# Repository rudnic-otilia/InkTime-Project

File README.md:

# InkTime

Smartwatch open-source bazat pe nRF52840, cu display e-paper.

## Diagramă Bloc

## BOM (Bill of Materials)

## Componente principale

| Referinta | Componenta | Descriere | Package | Cantitate | JLCPCB / LCSC | Datasheet |
|-----------|-----------|-----------|---------|-----------|---------------|-----------|
| U1 | NRF52840-QIAA-R | MCU principal + BLE 5.0 + USB nativ | aQFN-73 (7×7mm) | 1 | [C190794](https://jlcpcb.com/partdetail/NordicSemicon-NRF52840_QIAAR/C190794) | [Datasheet](https://infocenter.nordicsemi.com/pdf/nRF52840_PS_v1.7.pdf) |
| IC1 | BQ25180YBGR | Charger LiPo cu power-path, I2C | DSBGA-8 (1.6×1.1mm) | 1 | [C3682423](https://jlcpcb.com/partdetail/TexasInstruments-BQ25180YBGR/C3682423) | [Datasheet](https://www.ti.com/lit/ds/symlink/bq25180.pdf) |
| IC9 | RT6160AWSC | Buck-boost regulator 3.3V, I2C | WLCSP-15 (1.4×2.3mm) | 1 | [C7065276](https://jlcpcb.com/partdetail/RichTek-RT6160AWSC/C7065276) | [Datasheet](https://www.richtek.com/assets/product_file/RT6160A/DS6160A-00.pdf) |
| U3 | MAX17048G+T10 | Fuel gauge baterie LiPo, I2C | DFN-8 (2×2mm) | 1 | [C2682616](https://jlcpcb.com/partdetail/MaximIntegrated-MAX17048GT10/C2682616) | [Datasheet](https://www.analog.com/media/en/technical-documentation/data-sheets/MAX17048-MAX17049.pdf) |
| IC3 | BMA423 | Accelerometru 3-axe + pedometru, I2C | LGA-12 (2×2mm) | 1 | [C189517](https://jlcpcb.com/partdetail/BoschSensortec-BMA423/C189517) | [Datasheet](https://www.lcsc.com/datasheet/C189517.pdf) |
| IC2 | DRV2605YZFR | Haptic driver pentru motor ERM, I2C | DSBGA-9 (1.44×1.44mm) | 1 | [C81079](https://jlcpcb.com/partdetail/TexasInstruments-DRV2605YZFR/C81079) | [Datasheet](https://www.ti.com/lit/ds/symlink/drv2605.pdf) |
| D3 | USBLC6-2SC6Y | Protecție ESD linii USB D+/D- | SOT-23-6 | 1 | [C5310974](https://jlcpcb.com/partdetail/TECHPUBLIC-USBLC62SC6Y/C5310974) | [Datasheet](https://www.st.com/resource/en/datasheet/usblc6-2.pdf) |
| Q3 | SI1308EDL-T1-GE3 | N-channel MOSFET, power gate e-paper | SC-70-3 | 1 | [C10487](https://jlcpcb.com/partdetail/VishayIntertech-SI1308EDLT1GE3/C10487) | [Datasheet](https://www.vishay.com/docs/63587/si1308edl.pdf) |
| Q1 | DMG2305UX-7 | P-channel MOSFET, power switch | SOT-23-3 | 1 | [C252544](https://jlcpcb.com/partdetail/Diodes-DMG2305UXT116/C252544) | [Datasheet](https://www.diodes.com/assets/Datasheets/DMG2305UX.pdf) |
| J4 | KH-TYPE-C-16P | Conector USB-C 16 pini | SMD | 1 | [C2765186](https://jlcpcb.com/partdetail/Kinghelm-KH_TYPEC_16P/C2765186) | [Datasheet](https://www.kinghelm.net/usb-connectors/kh-type-c-16p.html) |
| J1 | 503480-2400 | Conector FPC 0.5mm 24 pini, pentru display e-paper | SMD | 1 | [C262280](https://jlcpcb.com/partdetail/Molex-5034802400/C262280) | [Datasheet](https://www.molex.com/en-us/products/part-detail/503480-2400) |
| J2 | TC2030-IDC | Conector Tag-Connect SWD debug/programare | PCB footprint | 1 | — | [Datasheet](https://www.tag-connect.com/wp-content/uploads/bsk-pdf-manager/TC2030-IDC_1.pdf) |
| ANT1 | 2450AT18B100E | Antenă chip 2.4GHz pentru BLE | SMD | 1 | [C89771](https://jlcpcb.com/partdetail/Johanson-2450AT18B100E/C89771) | [Datasheet](https://www.johansontechnology.com/datasheets/2450AT18B100E/2450AT18B100E.pdf) |
| X1 | X322516MLB4SI | Crystal HFXO 32MHz, 8pF, ±10ppm pentru nRF52840 | SMD 2016 | 1 | [C13738](https://jlcpcb.com/partdetail/YangxingTech-X322516MLB4SI/C13738) | [Datasheet](https://datasheet.lcsc.com/lcsc/2110221730_YXC-X322516MLB4SI_C13738.pdf) |
| X2 | Q13FC13500004 | Crystal LFXO 32.768kHz, 12.5pF, ±20ppm pentru RTC | SMD 3215 | 1 | [C32346](https://jlcpcb.com/partdetail/Epson-Q13FC13500004/C32346) | [Datasheet](https://www.lcsc.com/datasheet/C32346.pdf) |
| SW_UP, SW_DN, SW_ENT | EVP-AKE31A | Butoane tactile SMD | SMD | 3 | [C3669064](https://jlcpcb.com/partdetail/Panasonic-EVPAKE31A/C3669064) | [Datasheet](https://industrial.panasonic.com/cdbs/www-data/pdf/ATV0000/ATV0000CE5.pdf) |
| D2, D4, D5 | MBR0530 | Diodă Schottky 0.5A 30V, circuit drive e-paper | SOD-123 | 3 | [C424058](https://jlcpcb.com/partdetail/onsemi-MBR0530T1G/C424058) | [Datasheet](https://www.onsemi.com/pdf/datasheet/mbr0530t1-d.pdf) |
| L7 | FTC252012SR47MBCA | Inductor 0.47µH pentru DC/DC | 0402 | 1 | [C408368](https://jlcpcb.com/partdetail/C408368) | — |
| L5 | Inductor 68µH | Inductor boost pentru circuit drive e-paper | SMD | 1 | — | — |

---

## Pasive (rezistențe și condensatoare)

| Referință | Valoare | Package | Cantitate | Notă |
|-----------|---------|---------|-----------|------|
| C1, C2, C17, C18 | 12pF | 0201 / 0402 | 4 | Load caps cristale |
| C3, C4 | 1pF | 0201 | 2 | RF matching |
| C5, C7, C8, C12, C19 | 100nF | 0201 / 0402 | 5 | Decoupling MCU |
| C6, C20, C21, C14, C43 | 4.7µF | 0402 | 5 | Bulk decoupling |
| C9 | 820pF | 0201 | 1 | RF matching |
| C11 | 100pF | 0201 | 1 | Decoupling |
| C15 | 1.0µF | 0201 | 1 | Decoupling |
| C16 | 47nF | 0201 | 1 | Decoupling |
| C24, C39 | 10µF | 0402 | 2 | Bulk decoupling |
| C25, C33 | 22µF | 0402 | 2 | Output caps RT6160 |
| C23, C27, C34, C32, C37, C38 | 0.1µF / 1µF | 0201 | 6 | Decoupling PMIC |
| C29, C30, C31, C42 | 1µF / 0.1µF | 0201 | 4 | Decoupling diverși |
| C1-EP-DR | 10µF | 0402 | 1 | Circuit drive EPD |
| C2-EP-DR | 4.7µF/25V | 0402 | 1 | Circuit drive EPD |
| EPD_C1...C12 | 1µF/50V, 0.1µF/50V | 0402 | 10 | Condensatoare display |
| R17, R18 | 3K3 | 0201 | 2 | Pull-up I2C |
| R5, R7, R8, R9, R_PWR_EPD, R2_EP_DR | 10K | 0201 | 6 | Pull-up / bias |
| R1_USB, R2_USB | 5K1 | 0201 | 2 | CC pins USB-C |
| R_TYPE_SEL | 2.2Ω | 0201 | 1 | Selecție tip charger |
| R1_EP_DR | 0.47Ω | 0201 | 1 | Sense rezistor EPD |
| R2, R3, R4 | 0Ω | 0201 | 3 | Jumperi / DNP |
| L1 | 3.9nH | 0201 | 1 | RF matching |
| L2 | 10µH | 0402 | 1 | DC/DC inductor MCU |
| L3 | 15nH | 0402 | 1 | RF matching |

---

# Descriere Hardware

## MCU — nRF52840

Microcontrollerul principal este nRF52840 de la Nordic Semiconductor, un ARM Cortex-M4 la 64 MHz cu BLE 5.0 si USB nativ integrate. Are 1 MB Flash si 256 KB RAM. A fost ales pentru ca include tot ce e necesar intr-un singur chip: procesor, radio BLE si USB, ceea ce simplifica mult designul unui smartwatch.

Are doua cristale externe obligatorii: unul de 32 MHz pentru BLE si USB, si unul de 32.768 kHz pentru ceasul in timp real (RTC) care mentine ora cand dispozitivul doarme.

Consumul in deep sleep este sub 2 uA, ceea ce il face potrivit pentru un dispozitiv cu baterie mica.

---

## Magistrala I2C

Majoritatea componentelor comunica cu MCU-ul prin I2C pe pinii P0.06 (SDA) si P0.07 (SCL), cu rezistente pull-up de 3.3K. Fiecare componenta are o adresa unica:

| Componenta | Rol | Adresa |
|---|---|---|
| BQ25180 | Charger baterie | 0x6A |
| RT6160 | Regulator 3.3V | 0x75 |
| MAX17048 | Nivel baterie | 0x36 |
| BMA423 | Accelerometru | 0x18 |
| DRV2605 | Motor vibratii | 0x5A |

---

## Display E-Paper

Display-ul de 1.54" (200x200 pixeli) este conectat prin SPI (SCK pe P0.02, MOSI pe P0.03, plus pini de control CS/DC/RST/BUSY). Avantajul e-paper-ului este ca nu consuma energie cand imaginea sta pe loc — consuma doar la refresh.

Alimentarea display-ului este controlata printr-un MOSFET (P1.01) care il opreste complet intre refresh-uri. Se face un refresh partial o data pe minut pentru a actualiza ora, si un full refresh mai rar pentru a elimina ghosting-ul.

---

## Alimentare

Lantul de alimentare functioneaza asa: USB-C (5V) → BQ25180 (incarca bateria si alimenteaza sistemul) → RT6160 (converteste tensiunea bateriei la 3.3V fix) → toate componentele.

BQ25180 are un circuit de power-path, adica sistemul functioneaza si fara baterie daca e conectat la USB. MAX17048 masoara nivelul bateriei si trimite o intrerupere la MCU cand bateria e aproape descarcata.

Pe liniile USB exista o dioda ESD (USBLC6-2SC6Y) care protejeaza circuitul impotriva descarcarilor electrostatice.

---

## Senzori si periferice

**BMA423** — accelerometru cu pedometru hardware integrat. Numara pasii independent, fara sa trezeasca MCU-ul. Trezeste MCU-ul printr-o intrerupere pe P0.08 cand detecteaza miscare sau un anumit numar de pasi.

**DRV2605** — driver pentru motorul de vibratie. MCU-ul ii trimite prin I2C un ID de efect, iar DRV2605 il executa autonom din biblioteca sa de 123 de efecte stocate intern.

**Butoane** — trei butoane (Sus/Jos/Enter) conectate active-low la GND pe pinii P0.13, P0.14 si P1.00. Pot trezi MCU-ul din sleep.

---

## Consum estimat

| Stare | Curent | Timp/zi |
|---|---|---|
| Deep sleep | ~8 uA | ~24h |
| Refresh display (1x/min) | ~8 mA | ~60s total |
| Notificare (BLE + display + vibratii) | ~15 mA | ~100s total |

Total estimat: ~2 mAh/zi → pe o baterie de 250 mAh rezulta o autonomie teoretica de peste 100 de zile. In practica, cu pierderile reale, targetul este de 30 de zile conform specificatiilor proiectului.

# Pini nRF52840 folositi

## I2C — P0.06 (SDA) si P0.07 (SCL)

Acesti doi pini sunt folositi de toate componentele care comunica prin I2C: charger-ul BQ25180,
regulatorul RT6160, fuel gauge-ul MAX17048, accelerometrul BMA423 si driverul haptic DRV2605.
Sunt pini de uz general cu suport hardware I2C si sunt plasati convenabil in schema pentru
rutarea PCB-ului. Pull-up-urile de 3.3K sunt necesare pentru ca I2C are iesiri open-drain.

## SPI — P0.02 (SCK), P0.03 (MOSI), P0.05 (CS)

Folositi pentru comunicatia cu display-ul e-paper. SPI a fost ales in loc de I2C pentru display
deoarece este mult mai rapid, important la refresh-ul imaginii. CS (chip select) pe P0.05
activeaza display-ul doar cand MCU-ul vrea sa ii trimita date.

## Pini de control display — P0.15 (DC), P0.16 (RST), P0.17 (BUSY)

- **DC** (Data/Command): ii spune display-ului daca ce primeste este o comanda sau date de imagine
- **RST** (Reset): reseteaza display-ul la pornire sau dupa o eroare
- **BUSY**: display-ul tine acest pin activ cat timp proceseaza un refresh; MCU-ul asteapta sa
  se elibereze inainte sa trimita date noi

## Power gate display — P1.01

Controleaza MOSFET-ul care opreste alimentarea display-ului cand nu e folosit. Implicit OFF la
reset, activat doar in timpul unui refresh. Economiseste energie intre actualizari.

## Intreruperi

- **P0.08 — BMA423 INT1**: trezeste MCU-ul din deep sleep la detectia de miscare sau pas.
  Folosit ca sursa principala de wake-up pentru activitate fizica.
- **P1.08 — BMA423 INT2**: intrerupere secundara pentru evenimente avansate ale accelerometrului.
- **P0.10 — MAX17048 ALRT**: MCU-ul este notificat cand bateria scade sub un prag configurat,
  pentru a afisa avertismentul de baterie descarcata.
- **P0.11 — BQ25180 /INT**: notifica MCU-ul la evenimente de incarcare (USB conectat/deconectat,
  incarcare completa, eroare).

## Haptic enable — P0.12

Controleaza pinul EN al DRV2605. Cand nu e niciun eveniment haptic, acest pin e LOW si driverul
consuma sub 1 uA. MCU-ul il ridica la HIGH doar inainte sa trimita o comanda de vibratie.

## Butoane — P0.13, P0.14, P1.00

- **P0.13** — buton Sus
- **P0.14** — buton Jos
- **P1.00** — buton Enter / Esc

Toti trei sunt configurati cu pull-up intern si wake-on-low, adica o apasare de buton trezeste
MCU-ul direct din deep sleep fara consum suplimentar.

## USB — USBDP / USBDM (D+ / D-)

Pini dedicati USB ai nRF52840, rutati diferential la conectorul USB-C prin dioda ESD. Folositi
pentru programarea firmware-ului si optional pentru comunicatie cu PC-ul.

## SWD — SWDIO, SWDCLK, nRESET

Pini dedicati de debug si programare, conectati la conectorul TC2030. Folositi cu un programator
J-Link pentru a incarca firmware-ul si pentru debugging in timp real.

# Design Decisions — DRC Approved Errors

DRC-ul a returnat 0 erori si 85 aprobate. Motivele aprobarii:

- **Overlap (35) si Board Outline Clearance (40)**: provin din pozitia butoanelor, care a fost
  stabilita ca cerinta de proiect si nu poate fi modificata.

- **Copper Clearance (9)**: vias-uri care se intersecteaza

- **Copper - Restrict Clearance (1)**: zona restrictionata definita intentionat in jurul antenei
  BLE pentru izolarea ground plane-ului, conform recomandarilor Nordic Semiconductor.

Apache 2.0 — vezi [LICENSE](LICENSE)

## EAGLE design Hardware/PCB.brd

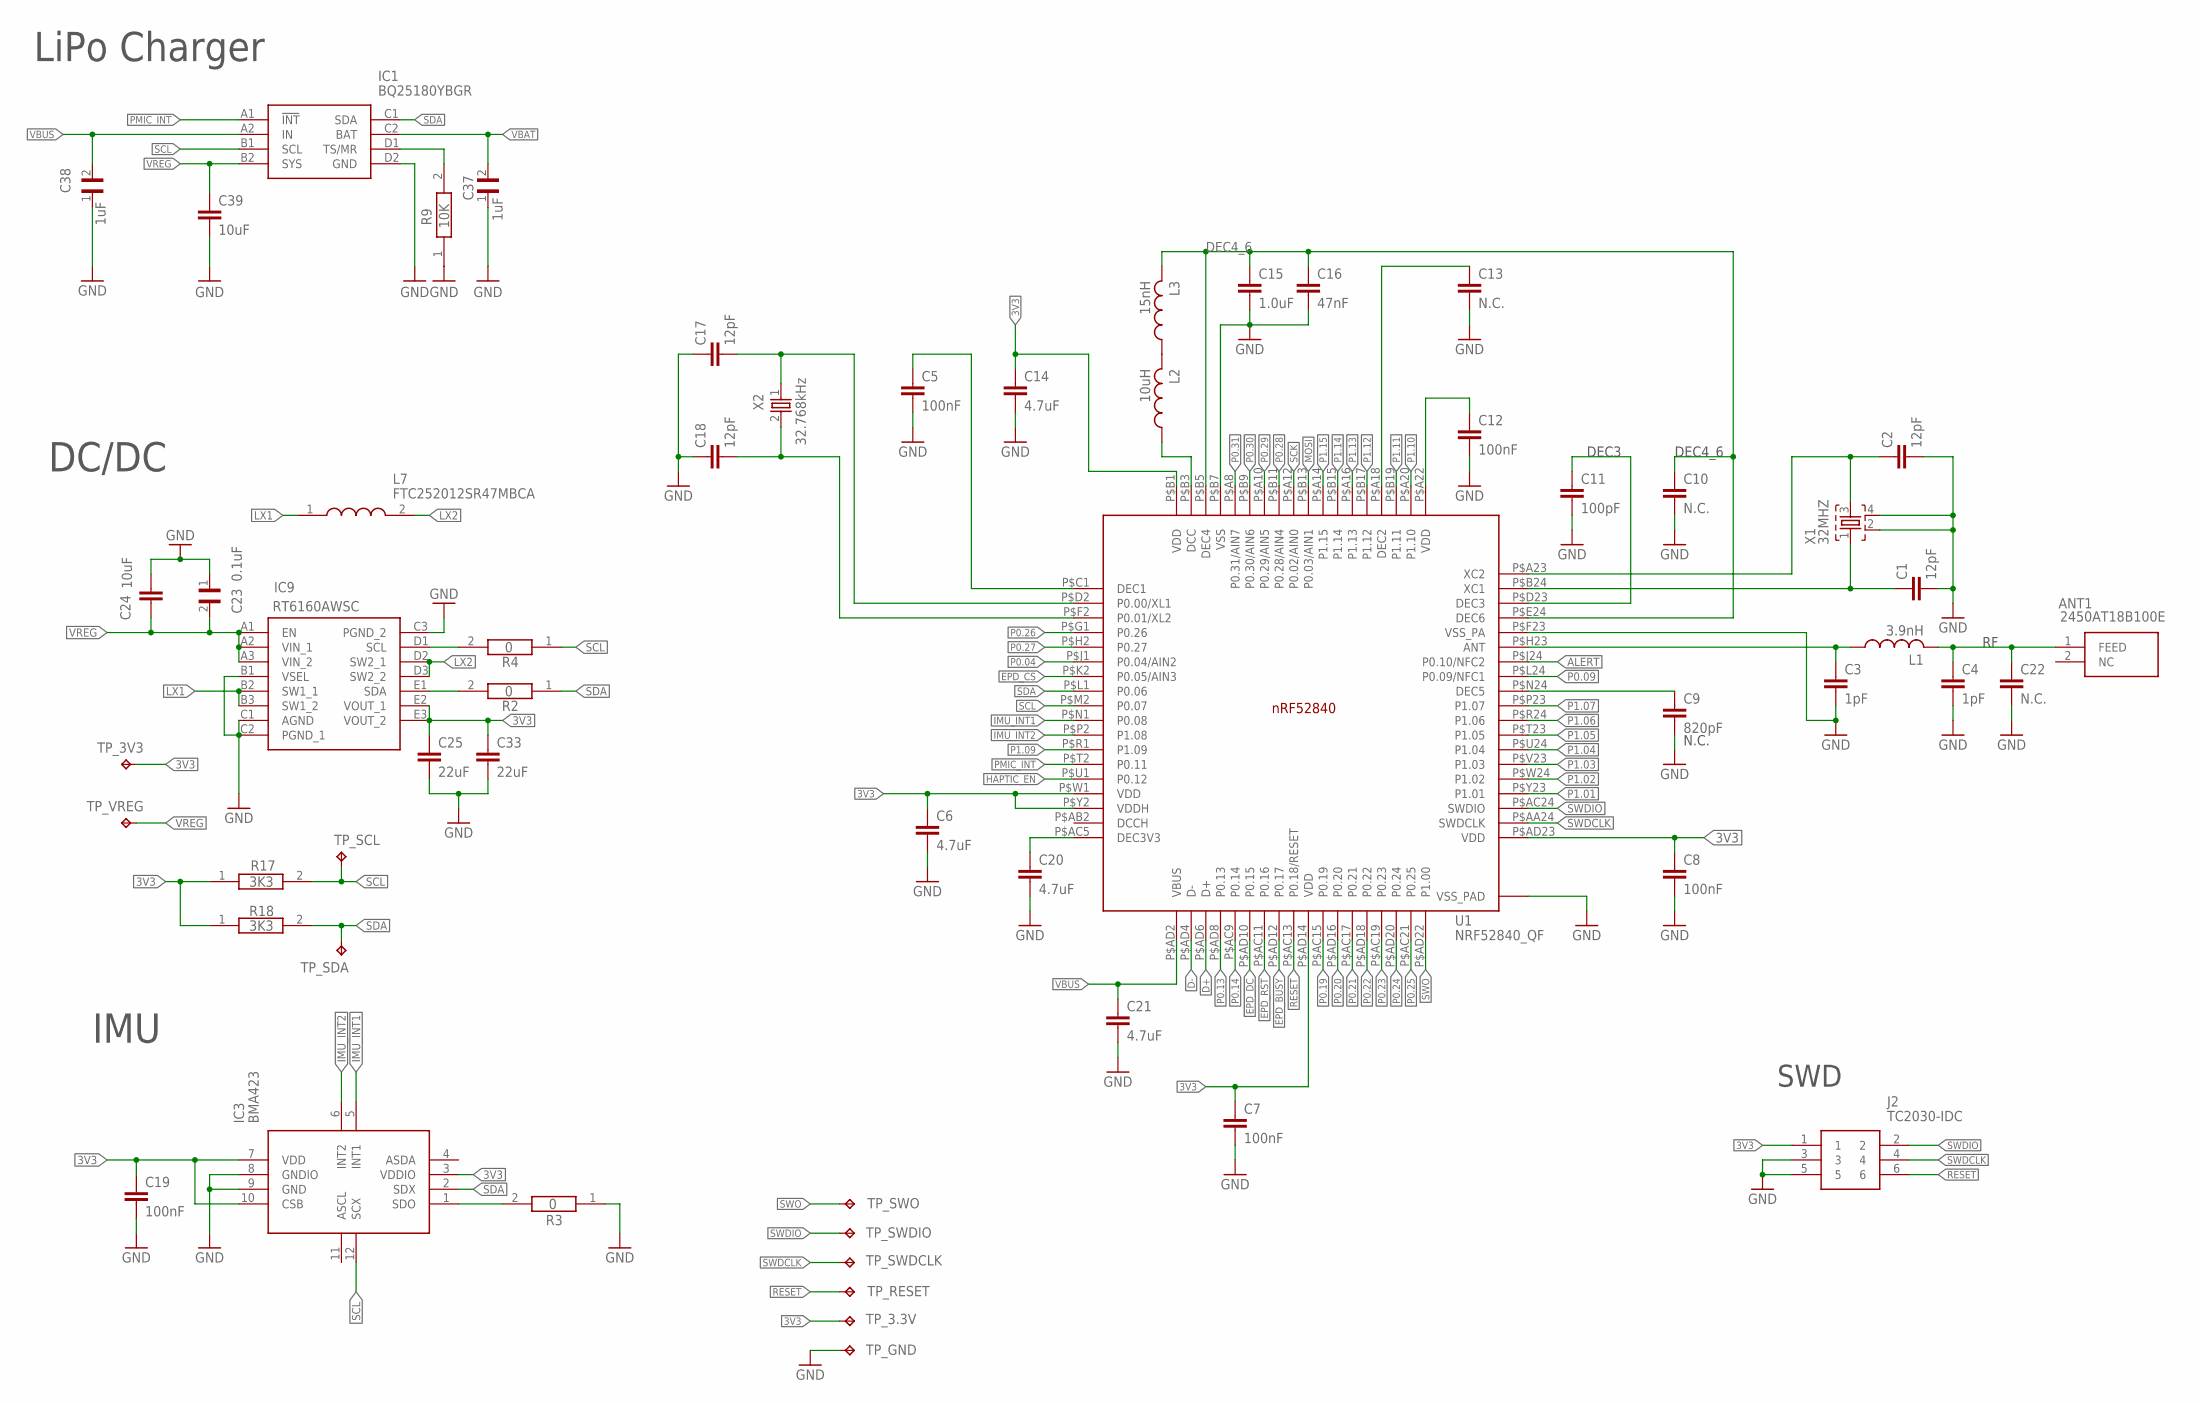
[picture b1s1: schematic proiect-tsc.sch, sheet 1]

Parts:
ANT1: 2450AT18B100E; 2450AT18B100E_ANTC3216X140N
C1, C2: 12pF; NORDIC_NRF_3_RESC0201_L
C3, C4: 1pF; NORDIC_NRF_3_RESC0201_L
C5, C7, C8, C12: 100nF; NORDIC_NRF_3_RESC0201_L
C6, C20, C21: 4.7uF; NORDIC_NRF_3_RESC0402_L
C9: 820pF; NORDIC_NRF_3_RESC0201_L
C10, C13, C22: N.C.; NORDIC_NRF_3_RESC0201_L
C11: 100pF; NORDIC_NRF_3_RESC0201_L
C14: 4.7uF; NORDIC_NRF_3_RESC0201_L
C15: 1.0uF; NORDIC_NRF_3_RESC0201_L
C16: 47nF; NORDIC_NRF_3_RESC0201_L
C17, C18: 12pF; PERFECT_0402_0402
C19: 100nF; PERFECT_0402_0402
C23: 0.1uF; GRM011R60J152KE01L_2_CAPC0201X13N
C24, C39: 10uF; PERFECT_0402_0402
C25, C33: 22uF; PERFECT_0402_0402
C37, C38: 1uF; GRM011R60J152KE01L_2_CAPC0201X13N
IC1: BQ25180YBGR; BQ25180YBGR_BGA8C40P2X4_100X155X50
IC3: BMA423; BMA423_BMA423
IC9: RT6160AWSC; RT6160AWSC_BGA15C40P3X5_140X230X60
J2: TC2030-IDC; TC2030-IDC_TC2030IDC
L1: 3.9nH; NORDIC_NRF_2_RESC0201_L
L2: 10uH; NORDIC_NRF_2_RESC0402_L
L3: 15nH; NORDIC_NRF_2_RESC0402_L
L7: FTC252012SR47MBCA; MLP2016SR47MT0S1_INDC2016X100N
R2, R4: 0; ERA-1AEB3401C_0201
R3: 0; CPF0201D7K68C1_0201
R9: 10K; CPF0201D7K68C1_0201
R17, R18: 3K3; CPF0201D7K68C1_0201
TP_3.3V, TP_3V3: HECTOR_WATCH_1_TPTP20R; HECTOR_WATCH_1_TP20R
TP_GND: HECTOR_WATCH_1_TPTP20R; HECTOR_WATCH_1_TP20R
TP_RESET: HECTOR_WATCH_1_TPTP20R; HECTOR_WATCH_1_TP20R
TP_SCL: HECTOR_WATCH_1_TPTP20R; HECTOR_WATCH_1_TP20R
TP_SDA: HECTOR_WATCH_1_TPTP20R; HECTOR_WATCH_1_TP20R
TP_SWDCLK: HECTOR_WATCH_1_TPTP20R; HECTOR_WATCH_1_TP20R
TP_SWDIO: HECTOR_WATCH_1_TPTP20R; HECTOR_WATCH_1_TP20R
TP_SWO: HECTOR_WATCH_1_TPTP20R; HECTOR_WATCH_1_TP20R
TP_VREG: HECTOR_WATCH_1_TPTP20R; HECTOR_WATCH_1_TP20R
U1: NRF52840_QF; NORDIC_NRF_4_AQFN50P700X700X85_HS-74N
X1: 32MHZ; NORDIC_NRF_BT-XTAL_2016_N
X2: 32.768kHz; NORDIC_NRF_1_XTAL_3215_N

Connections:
3V3: C6.1, C7.1, C8.1, C14.1, C19.1, C25.1, C33.1, IC3.3 (VDDIO), IC3.7 (VDD), IC3.10 (CSB), IC9.E2 (VOUT_1), IC9.E3 (VOUT_2), J2.1, R17.1, R18.1, TP_3.3V.TP, TP_3V3.TP, U1.P$AD14 (VDD), U1.P$AD23 (VDD), U1.P$B1 (VDD), U1.P$W1 (VDD), U1.P$Y2 (VDDH); also elsewhere on the board
ALERT: U1.P$J24 (P0.10/NFC2); also elsewhere on the board
D+: U1.P$AD6 (D+); also elsewhere on the board
D-: U1.P$AD4 (D-); also elsewhere on the board
DEC4_6: C10.1, C15.1, C16.1, L3.2, U1.P$B5 (DEC4), U1.P$E24 (DEC6)
EPD_BUSY: U1.P$AD12 (P0.17); also elsewhere on the board
EPD_CS: U1.P$K2 (P0.05/AIN3); also elsewhere on the board
EPD_DC: U1.P$AD10 (P0.15); also elsewhere on the board
EPD_RST: U1.P$AC11 (P0.16); also elsewhere on the board
GND: C1.2, C2.2, C3.2, C4.2, C5.2, C6.2, C7.2, C8.2, C9.2, C10.2, C11.2, C12.2, C13.2, C14.2, C15.2, C16.2, C17.1, C18.1, C19.2, C20.2, C21.2, C22.2, C23.1, C24.1, C25.2, C33.2, C37.1, C38.1, C39.2, IC1.D2 (GND), IC3.8 (GNDIO), IC3.9 (GND), IC9.B1 (VSEL), IC9.C1 (AGND), IC9.C2 (PGND_1), IC9.C3 (PGND_2), J2.3, J2.5, R3.1, R9.1, TP_GND.TP, U1.P$74 (VSS_PAD), U1.P$75 (VSS_PAD), U1.P$76 (VSS_PAD), U1.P$77 (VSS_PAD), U1.P$78 (VSS_PAD), U1.P$79 (VSS_PAD), U1.P$80 (VSS_PAD), U1.P$81 (VSS_PAD), U1.P$82 (VSS_PAD), U1.P$83 (VSS_PAD), U1.P$84 (VSS_PAD), U1.P$85 (VSS_PAD), U1.P$86 (VSS_PAD), U1.P$87 (VSS_PAD), U1.P$88 (VSS_PAD), U1.P$89 (VSS_PAD), U1.P$90 (VSS_PAD), U1.P$B7 (VSS), U1.P$F23 (VSS_PA), X1.2, X1.4; also elsewhere on the board
HAPTIC_EN: U1.P$U1 (P0.12); also elsewhere on the board
IMU_INT1: IC3.5 (INT1), U1.P$N1 (P0.08)
IMU_INT2: IC3.6 (INT2), U1.P$P2 (P1.08)
LX1: IC9.B2 (SW1_1), IC9.B3 (SW1_2), L7.1
LX2: IC9.D2 (SW2_1), IC9.D3 (SW2_2), L7.2
MOSI: U1.P$B13 (P0.03/AIN1); also elsewhere on the board
unnamed: IC1.D1 (TS/MR), R9.2
unnamed: C11.1, U1.P$D23 (DEC3)
unnamed: IC9.D1 (SCL), R4.2
unnamed: IC9.E1 (SDA), R2.2
unnamed: C18.2, U1.P$F2 (P0.01/XL2), X2.2
unnamed: C17.2, U1.P$D2 (P0.00/XL1), X2.1
unnamed: IC3.1 (SDO), R3.2
unnamed: C5.1, U1.P$C1 (DEC1)
unnamed: L2.1, U1.P$B3 (DCC)
unnamed: L2.2, L3.1
unnamed: C12.1, U1.P$A22 (VDD)
unnamed: C13.1, U1.P$A18 (DEC2)
unnamed: C2.1, U1.P$A23 (XC2), X1.3
unnamed: C1.1, U1.P$B24 (XC1), X1.1
unnamed: C3.1, L1.1, U1.P$H23 (ANT)
unnamed: ANT1.1 (FEED), C4.1, C22.1, L1.2
unnamed: C9.1, U1.P$N24 (DEC5)
unnamed: C20.1, U1.P$AC5 (DEC3V3)
P0.04: U1.P$J1 (P0.04/AIN2)
P0.09: U1.P$L24 (P0.09/NFC1)
P0.13: U1.P$AD8 (P0.13)
P0.14: U1.P$AC9 (P0.14)
P0.19: U1.P$AC15 (P0.19)
P0.20: U1.P$AD16 (P0.20)
P0.21: U1.P$AC17 (P0.21)
P0.22: U1.P$AD18 (P0.22)
P0.23: U1.P$AC19 (P0.23)
P0.24: U1.P$AD20 (P0.24)
P0.25: U1.P$AC21 (P0.25)
P0.26: U1.P$G1 (P0.26)
P0.27: U1.P$H2 (P0.27)
P0.28: U1.P$B11 (P0.28/AIN4)
P0.29: U1.P$A10 (P0.29/AIN5)
P0.30: U1.P$B9 (P0.30/AIN6)
P0.31: U1.P$A8 (P0.31/AIN7)
P1.01: U1.P$Y23 (P1.01); also elsewhere on the board
P1.02: U1.P$W24 (P1.02); also elsewhere on the board
P1.03: U1.P$V23 (P1.03)
P1.04: U1.P$U24 (P1.04)
P1.05: U1.P$T23 (P1.05)
P1.06: U1.P$R24 (P1.06)
P1.07: U1.P$P23 (P1.07)
P1.09: U1.P$R1 (P1.09)
P1.10: U1.P$A20 (P1.10)
P1.11: U1.P$B19 (P1.11)
P1.12: U1.P$B17 (P1.12)
P1.13: U1.P$A16 (P1.13)
P1.14: U1.P$B15 (P1.14)
P1.15: U1.P$A14 (P1.15)
PMIC_INT: IC1.A1 (!INT), U1.P$T2 (P0.11)
RESET: J2.6, TP_RESET.TP, U1.P$AC13 (P0.18/RESET)
SCK: U1.P$A12 (P0.02/AIN0); also elsewhere on the board
SCL: IC1.B1 (SCL), IC3.12 (SCX), R4.1, R17.2, TP_SCL.TP, U1.P$M2 (P0.07); also elsewhere on the board
SDA: IC1.C1 (SDA), IC3.2 (SDX), R2.1, R18.2, TP_SDA.TP, U1.P$L1 (P0.06); also elsewhere on the board
SWDCLK: J2.4, TP_SWDCLK.TP, U1.P$AA24 (SWDCLK)
SWDIO: J2.2, TP_SWDIO.TP, U1.P$AC24 (SWDIO)
SWO: TP_SWO.TP, U1.P$AD22 (P1.00)
VBAT: C37.2, IC1.C2 (BAT); also elsewhere on the board
VBUS: C21.1, C38.2, IC1.A2 (IN), U1.P$AD2 (VBUS); also elsewhere on the board
VREG: C23.2, C24.2, C39.1, IC1.B2 (SYS), IC9.A1 (EN), IC9.A2 (VIN_1), IC9.A3 (VIN_2), TP_VREG.TP

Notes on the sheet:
LiPo Charger
DC/DC
IMU
DEC3
DEC4_6
N.C.
SWD

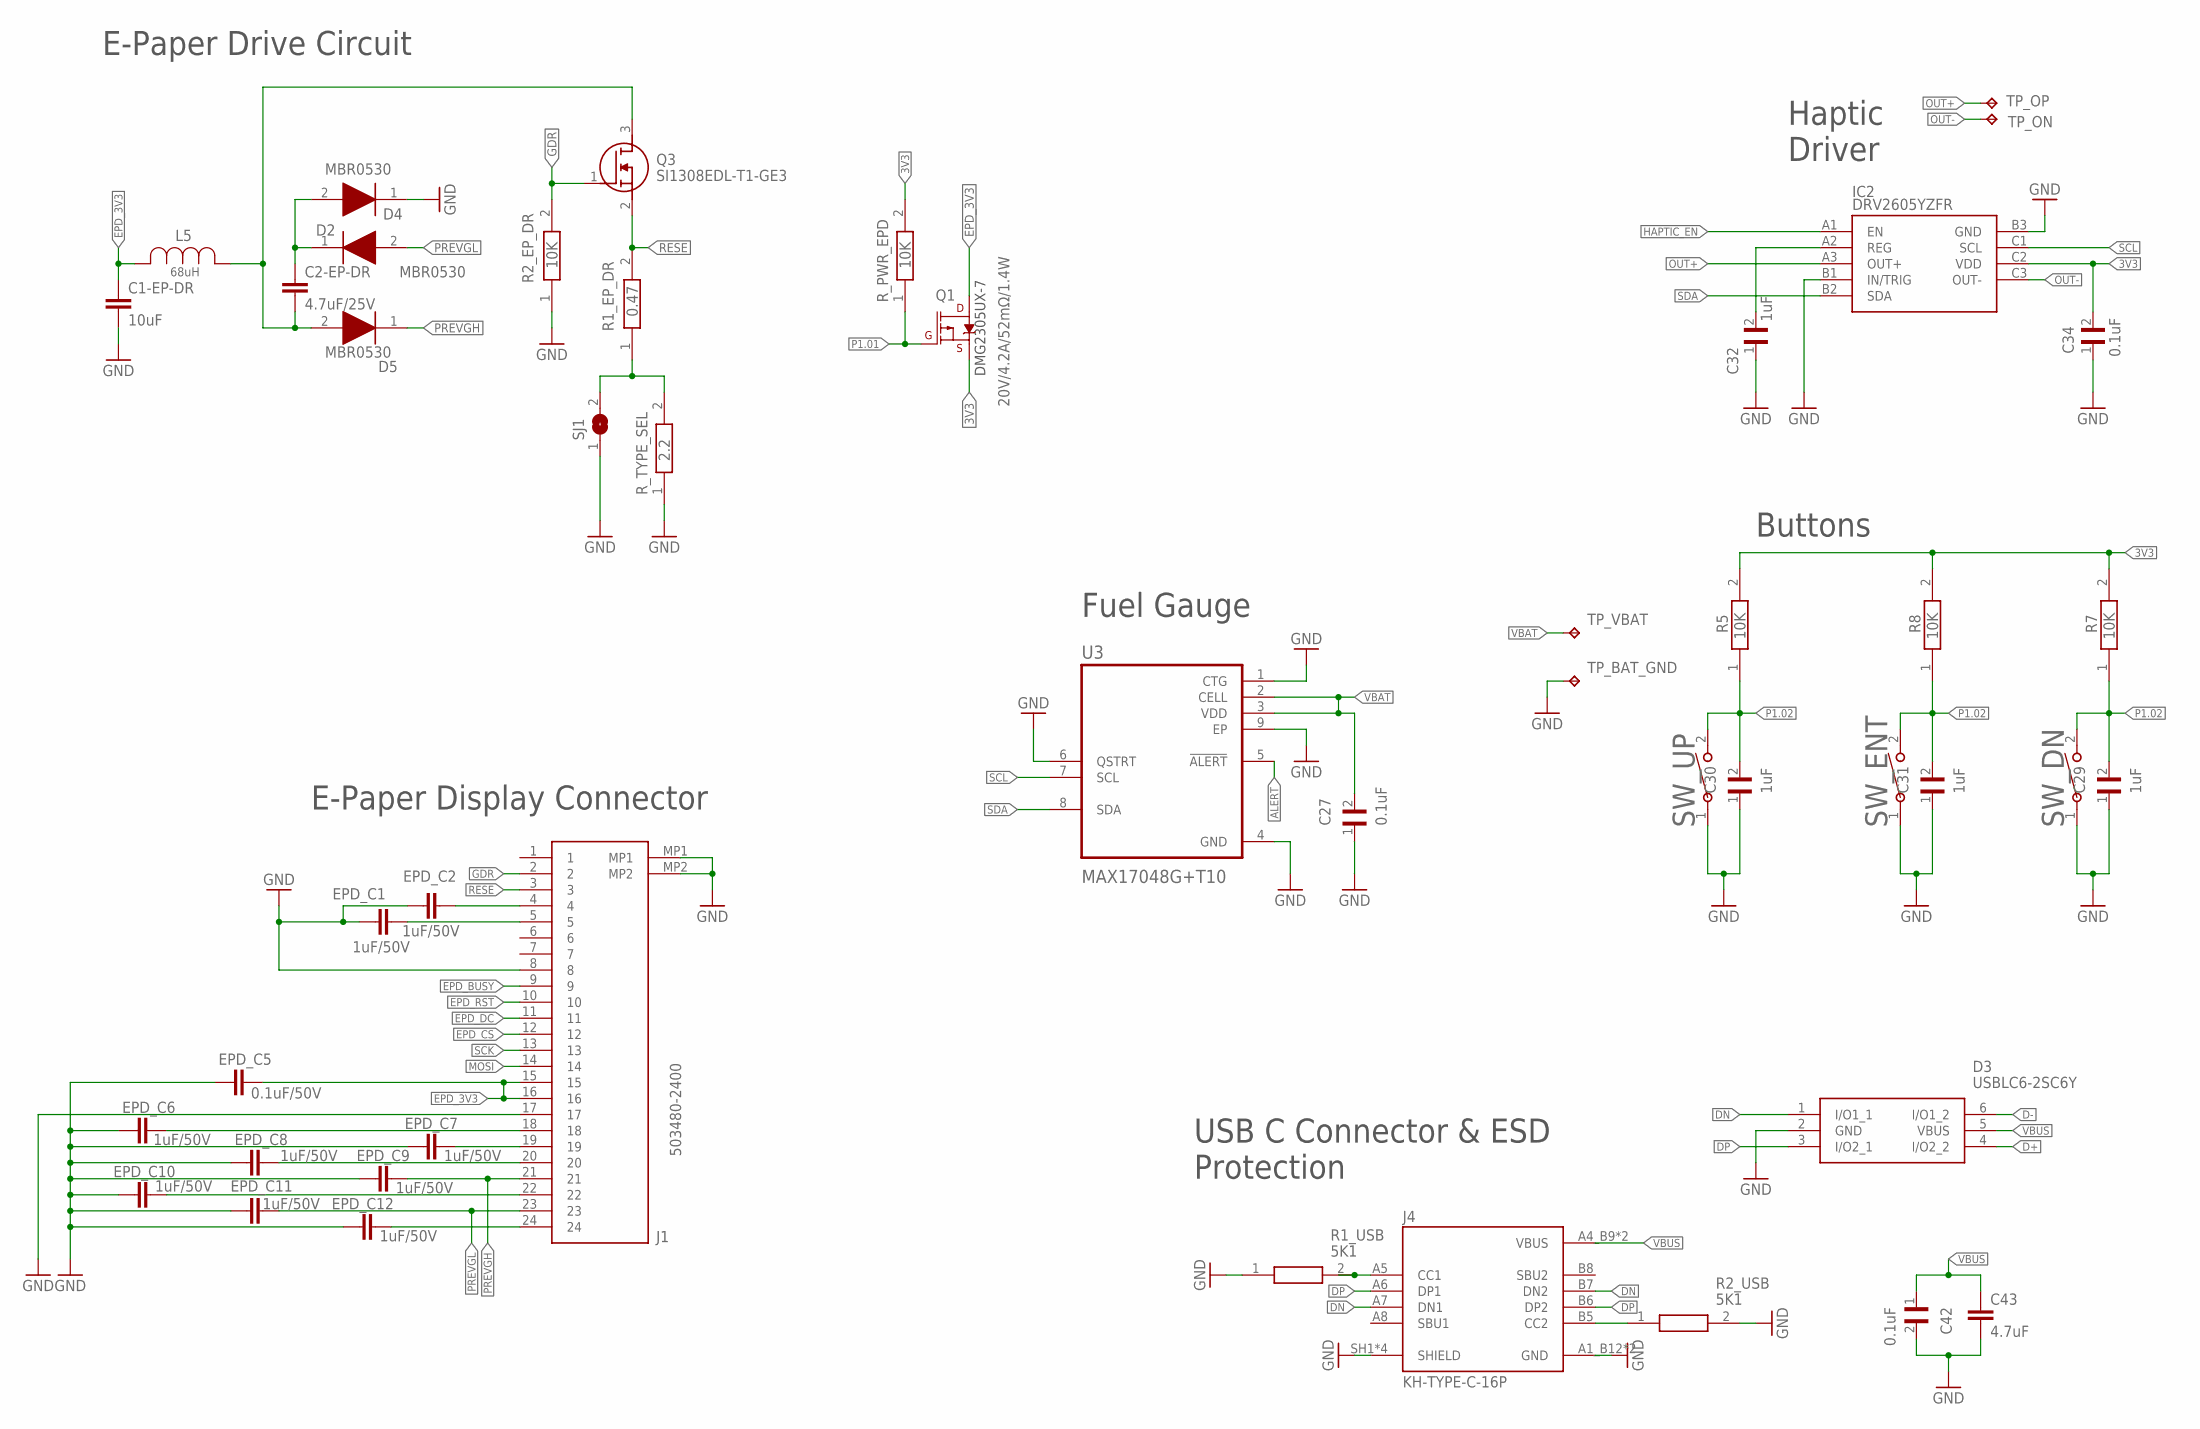
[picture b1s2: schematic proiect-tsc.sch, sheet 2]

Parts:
C1-EP-DR: 10uF; NORDIC_NRF_3_RESC0402_L
C2-EP-DR: 4.7uF/25V; NORDIC_NRF_3_RESC0402_L
C27, C34: 0.1uF; GRM011R60J152KE01L_2_CAPC0201X13N
C29, C30, C31: 1uF; GRM011R60J152KE01L_1_0201
C32: 1uF; GRM011R60J152KE01L_2_CAPC0201X13N
C42: 0.1uF; GRM011R60J152KE01L_1_0201
C43: 4.7uF; PERFECT_0402_0402
D2, D4, D5: MBR0530; ESP32_C6_LIBRARY_5_SOD3716X135N
D3: USBLC6-2SC6Y; ESP32_C6_LIBRARY_3_SOT95P280X145-6N
EPD_C1, EPD_C2, EPD_C6, EPD_C7, EPD_C8, EPD_C9, EPD_C10, EPD_C11, EPD_C12: 1uF/50V; NORDIC_NRF_3_RESC0402_L
EPD_C5: 0.1uF/50V; NORDIC_NRF_3_RESC0402_L
IC2: DRV2605YZFR; DRV2605YZFR_BGA9C50P3X3_144X144X62
J1: 503480-2400; 503480-2400_5034802400
J4: KH-TYPE-C-16P; KH-TYPE-C-16P_KINGHELM_KH-TYPE-C-16P
L5: 68uH; ESP32_C6_LIBRARY_2_IND_4828-WE-TPC_WRE
Q1: 20V/4.2A/52mΩ/1.4W; ESP32_C6_LIBRARY_4_ESP32_C6_LIBRARY_4_ESP32_C6_LIBRARY_4_ES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
Q3: SI1308EDL-T1-GE3; ESP32_C6_LIBRARY_6_SOT65P210X110-3N
R1_EP_DR: 0.47; CPF0201D7K68C1_0201
R1_USB, R2_USB: 5K1; CPF0201D7K68C1_0201
R2_EP_DR, R5, R7, R8: 10K; CPF0201D7K68C1_0201
R_PWR_EPD: 10K; CPF0201D7K68C1_0201
R_TYPE_SEL: 2.2; CPF0201D7K68C1_0201
SJ1: ESP32_C6_LIBRARY_7_JUMPER_SJ
SW_DN: 2025-10-22_07-23-44_LIBRARY_EVP-AKE31ASW_EVP-AKE3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; 2025-10-22_07-23-44_LIBRARY_SW_EVP-AKE31A_PAN
SW_ENT: 2025-10-22_07-23-44_LIBRARY_EVP-AKE31ASW_EVP-AKE3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; 2025-10-22_07-23-44_LIBRARY_SW_EVP-AKE31A_PAN
SW_UP: 2025-10-22_07-23-44_LIBRARY_EVP-AKE31ASW_EVP-AKE3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; 2025-10-22_07-23-44_LIBRARY_SW_EVP-AKE31A_PAN
TP_BAT_GND: HECTOR_WATCH_1_TPTP20R; HECTOR_WATCH_1_TP20R
TP_ON: HECTOR_WATCH_1_TPTP20R; HECTOR_WATCH_1_TP20R
TP_OP: HECTOR_WATCH_1_TPTP20R; HECTOR_WATCH_1_TP20R
TP_VBAT: HECTOR_WATCH_1_TPTP20R; HECTOR_WATCH_1_TP20R
U3: MAX17048G+T10; ESP32_C6_LIBRARY_SON50P200X200X80-9N

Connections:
3V3: C34.2, IC2.C2 (VDD), Q1.2 (S), R5.2, R7.2, R8.2, R_PWR_EPD.2; also elsewhere on the board
ALERT: U3.5 (!ALERT); also elsewhere on the board
D+: D3.4 (I/O2_2); also elsewhere on the board
D-: D3.6 (I/O1_2); also elsewhere on the board
DN: D3.1 (I/O1_1), J4.A7 (DN1), J4.B7 (DN2)
DP: D3.3 (I/O2_1), J4.A6 (DP1), J4.B6 (DP2)
EPD_3V3: C1-EP-DR.1, EPD_C5.2, J1.15, J1.16, L5.2, Q1.3 (D)
EPD_BUSY: J1.9; also elsewhere on the board
EPD_CS: J1.12; also elsewhere on the board
EPD_DC: J1.11; also elsewhere on the board
EPD_RST: J1.10; also elsewhere on the board
GDR: J1.2, Q3.1 (G), R2_EP_DR.2
GND: C1-EP-DR.2, C27.1, C29.1, C30.1, C31.1, C32.1, C34.1, C42.2, C43.2, D3.2 (GND), D4.1 (K), EPD_C1.1, EPD_C2.1, EPD_C5.1, EPD_C6.1, EPD_C7.1, EPD_C8.1, EPD_C9.1, EPD_C10.1, EPD_C11.1, EPD_C12.1, IC2.B1 (IN/TRIG), IC2.B3 (GND), J1.8, J1.17, J1.MP1, J1.MP2, J4.A1_B12 (GND), J4.A12_B1 (GND), J4.SH1 (SHIELD), J4.SH2 (SHIELD), J4.SH3 (SHIELD), J4.SH4 (SHIELD), R1_USB.1, R2_EP_DR.1, R2_USB.2, R_TYPE_SEL.1, SJ1.1, SW_DN.1, SW_ENT.1, SW_UP.1, TP_BAT_GND.TP, U3.1 (CTG), U3.4 (GND), U3.6 (QSTRT), U3.9 (EP); also elsewhere on the board
HAPTIC_EN: IC2.A1 (EN); also elsewhere on the board
MOSI: J1.14; also elsewhere on the board
unnamed: C2-EP-DR.2, D5.2 (A), L5.1, Q3.3 (D)
unnamed: C2-EP-DR.1, D2.1 (K), D4.2 (A)
unnamed: R1_EP_DR.1, R_TYPE_SEL.2, SJ1.2
unnamed: EPD_C2.2, J1.4
unnamed: EPD_C7.2, J1.19
unnamed: EPD_C1.2, J1.5
unnamed: C32.2, IC2.A2 (REG)
unnamed: EPD_C12.2, J1.24
unnamed: J4.B5 (CC2), R2_USB.1
unnamed: EPD_C8.2, J1.20
unnamed: EPD_C10.2, J1.22
unnamed: EPD_C6.2, J1.18
unnamed: J4.A5 (CC1), R1_USB.2
OUT+: IC2.A3 (OUT+), TP_OP.TP
OUT-: IC2.C3 (OUT-), TP_ON.TP
P1.01: Q1.1 (G), R_PWR_EPD.1; also elsewhere on the board
P1.02: C29.2, C30.2, C31.2, R5.1, R7.1, R8.1, SW_DN.2, SW_ENT.2, SW_UP.2; also elsewhere on the board
PREVGH: D5.1 (K), EPD_C9.2, J1.21
PREVGL: D2.2 (A), EPD_C11.2, J1.23
RESE: J1.3, Q3.2 (S), R1_EP_DR.2
SCK: J1.13; also elsewhere on the board
SCL: IC2.C1 (SCL), U3.7 (SCL); also elsewhere on the board
SDA: IC2.B2 (SDA), U3.8 (SDA); also elsewhere on the board
VBAT: C27.2, TP_VBAT.TP, U3.2 (CELL), U3.3 (VDD); also elsewhere on the board
VBUS: C42.1, C43.1, D3.5 (VBUS), J4.A4_B9 (VBUS), J4.A9_B4 (VBUS); also elsewhere on the board

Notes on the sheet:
E-Paper Drive Circuit
DMG2305UX-7
E-Paper Display Connector
Haptic Driver
Buttons
USB C Connector & ESD Protection
Fuel Gauge

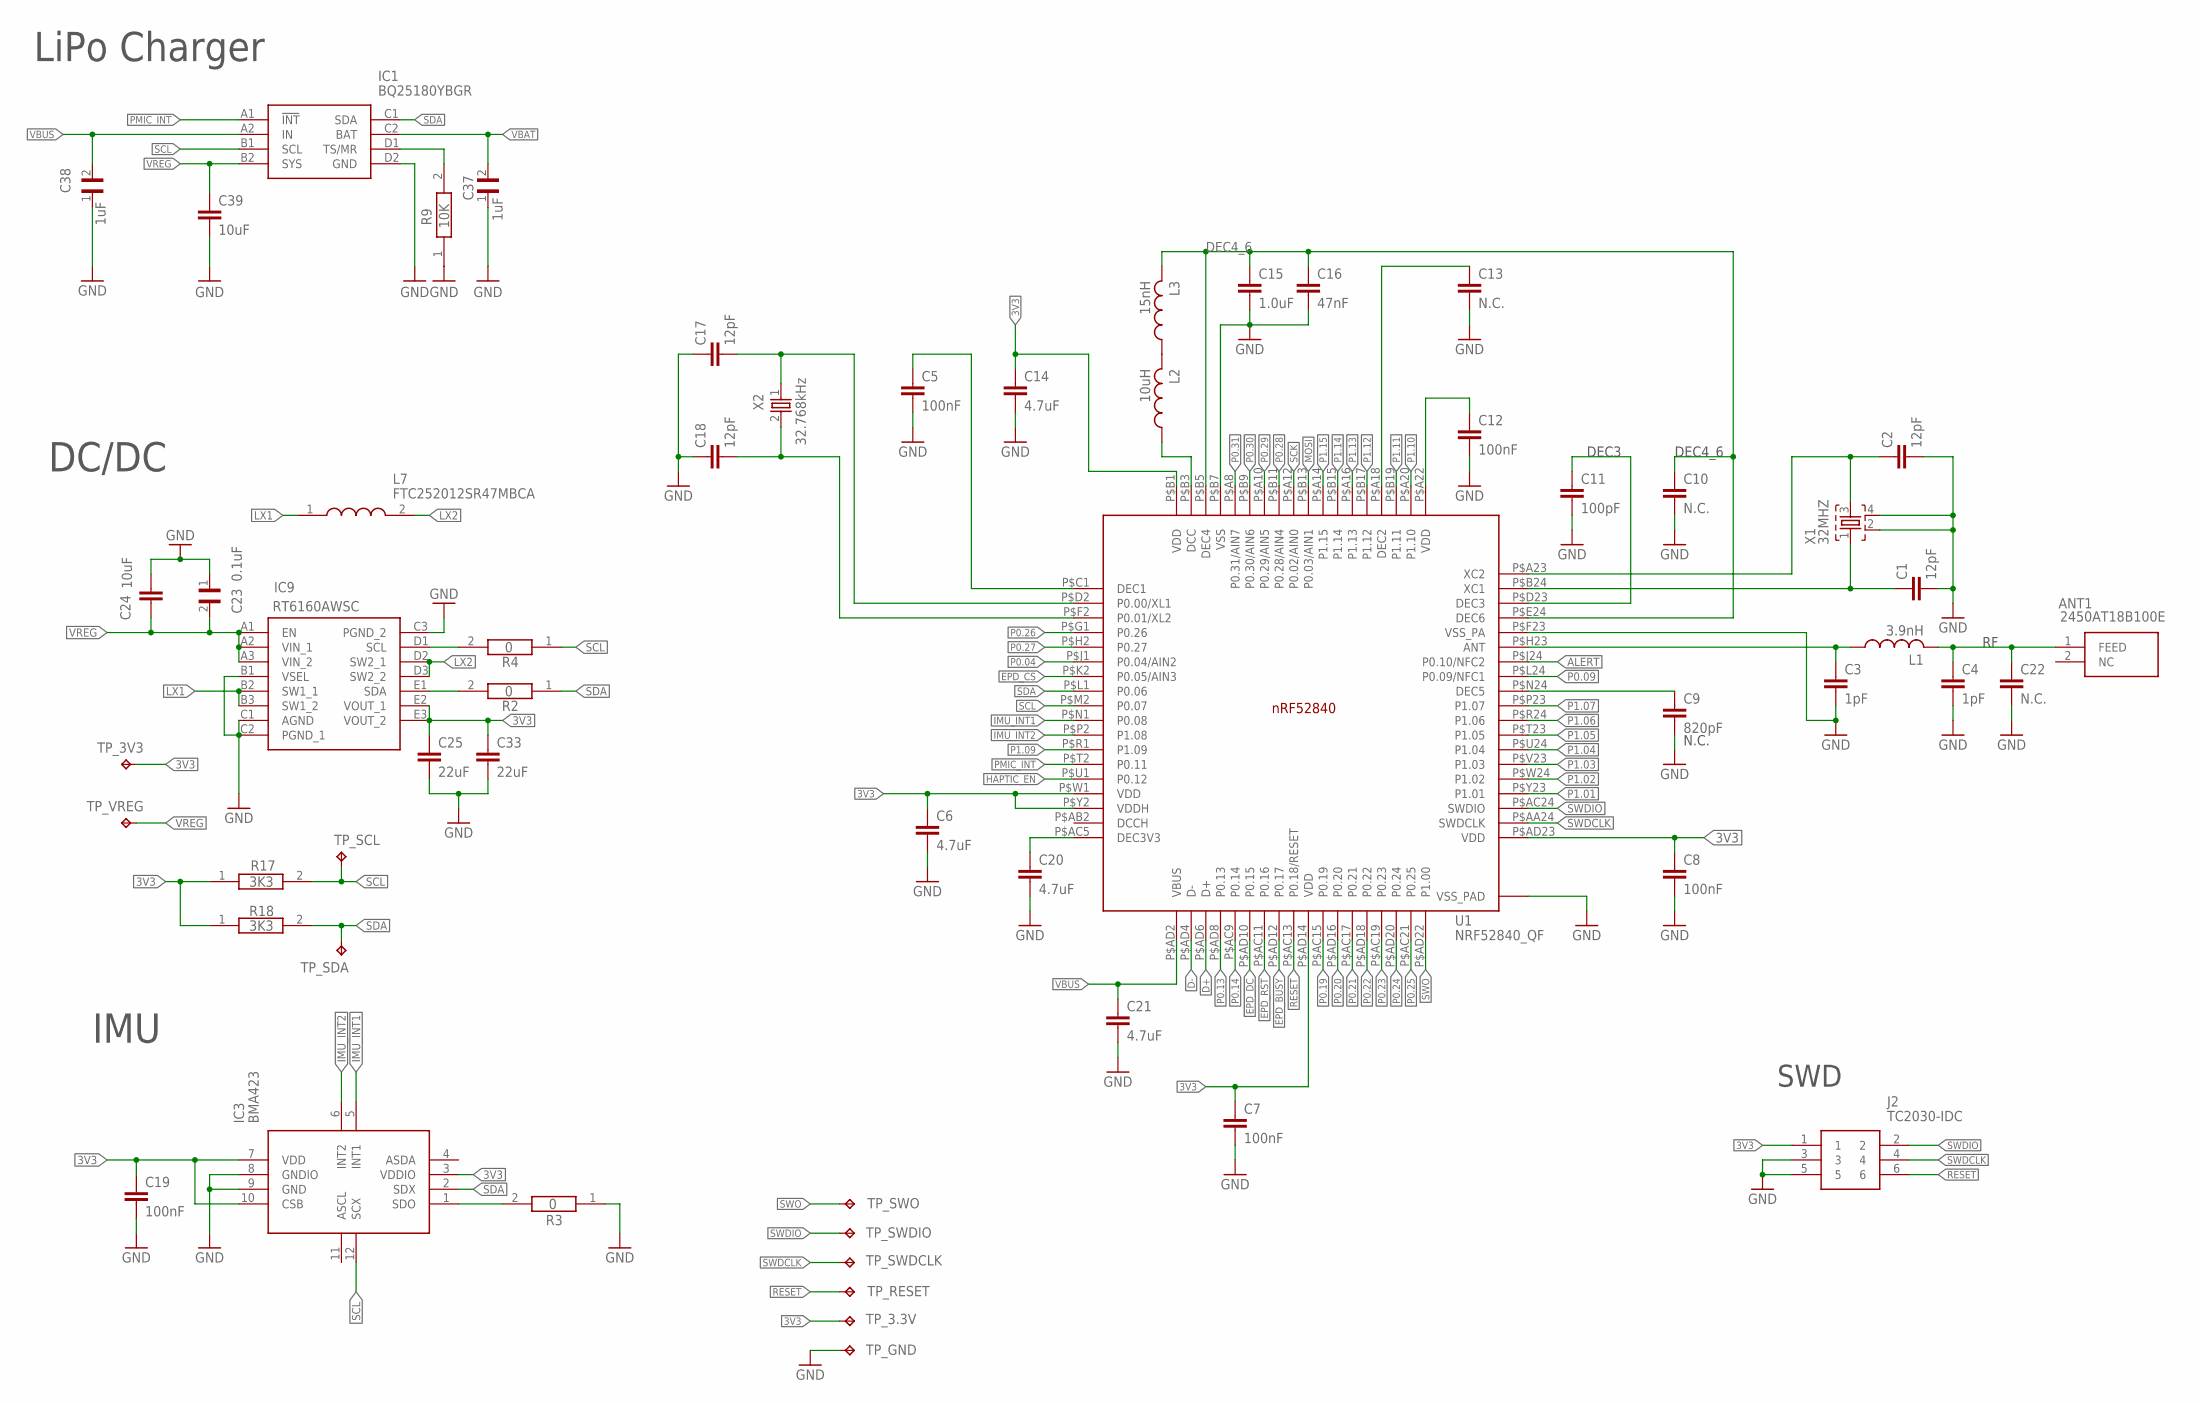
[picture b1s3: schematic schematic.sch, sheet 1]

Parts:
ANT1: 2450AT18B100E; 2450AT18B100E_ANTC3216X140N
C1, C2: 12pF; NORDIC_NRF_3_RESC0201_L
C3, C4: 1pF; NORDIC_NRF_3_RESC0201_L
C5, C7, C8, C12: 100nF; NORDIC_NRF_3_RESC0201_L
C6, C20, C21: 4.7uF; NORDIC_NRF_3_RESC0402_L
C9: 820pF; NORDIC_NRF_3_RESC0201_L
C10, C13, C22: N.C.; NORDIC_NRF_3_RESC0201_L
C11: 100pF; NORDIC_NRF_3_RESC0201_L
C14: 4.7uF; NORDIC_NRF_3_RESC0201_L
C15: 1.0uF; NORDIC_NRF_3_RESC0201_L
C16: 47nF; NORDIC_NRF_3_RESC0201_L
C17, C18: 12pF; PERFECT_0402_0402
C19: 100nF; PERFECT_0402_0402
C23: 0.1uF; GRM011R60J152KE01L_2_CAPC0201X13N
C24, C39: 10uF; PERFECT_0402_0402
C25, C33: 22uF; PERFECT_0402_0402
C37, C38: 1uF; GRM011R60J152KE01L_2_CAPC0201X13N
IC1: BQ25180YBGR; BQ25180YBGR_BGA8C40P2X4_100X155X50
IC3: BMA423; BMA423_BMA423
IC9: RT6160AWSC; RT6160AWSC_BGA15C40P3X5_140X230X60
J2: TC2030-IDC; TC2030-IDC_TC2030IDC
L1: 3.9nH; NORDIC_NRF_2_RESC0201_L
L2: 10uH; NORDIC_NRF_2_RESC0402_L
L3: 15nH; NORDIC_NRF_2_RESC0402_L
L7: FTC252012SR47MBCA; MLP2016SR47MT0S1_INDC2016X100N
R2, R4: 0; ERA-1AEB3401C_0201
R3: 0; CPF0201D7K68C1_0201
R9: 10K; CPF0201D7K68C1_0201
R17, R18: 3K3; CPF0201D7K68C1_0201
TP_3.3V, TP_3V3: HECTOR_WATCH_1_TPTP20R; HECTOR_WATCH_1_TP20R
TP_GND: HECTOR_WATCH_1_TPTP20R; HECTOR_WATCH_1_TP20R
TP_RESET: HECTOR_WATCH_1_TPTP20R; HECTOR_WATCH_1_TP20R
TP_SCL: HECTOR_WATCH_1_TPTP20R; HECTOR_WATCH_1_TP20R
TP_SDA: HECTOR_WATCH_1_TPTP20R; HECTOR_WATCH_1_TP20R
TP_SWDCLK: HECTOR_WATCH_1_TPTP20R; HECTOR_WATCH_1_TP20R
TP_SWDIO: HECTOR_WATCH_1_TPTP20R; HECTOR_WATCH_1_TP20R
TP_SWO: HECTOR_WATCH_1_TPTP20R; HECTOR_WATCH_1_TP20R
TP_VREG: HECTOR_WATCH_1_TPTP20R; HECTOR_WATCH_1_TP20R
U1: NRF52840_QF; NORDIC_NRF_4_AQFN50P700X700X85_HS-74N
X1: 32MHZ; NORDIC_NRF_BT-XTAL_2016_N
X2: 32.768kHz; NORDIC_NRF_1_XTAL_3215_N

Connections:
3V3: C6.1, C7.1, C8.1, C14.1, C19.1, C25.1, C33.1, IC3.3 (VDDIO), IC3.7 (VDD), IC3.10 (CSB), IC9.E2 (VOUT_1), IC9.E3 (VOUT_2), J2.1, R17.1, R18.1, TP_3.3V.TP, TP_3V3.TP, U1.P$AD14 (VDD), U1.P$AD23 (VDD), U1.P$B1 (VDD), U1.P$W1 (VDD), U1.P$Y2 (VDDH); also elsewhere on the board
ALERT: U1.P$J24 (P0.10/NFC2); also elsewhere on the board
D+: U1.P$AD6 (D+); also elsewhere on the board
D-: U1.P$AD4 (D-); also elsewhere on the board
DEC4_6: C10.1, C15.1, C16.1, L3.2, U1.P$B5 (DEC4), U1.P$E24 (DEC6)
EPD_BUSY: U1.P$AD12 (P0.17); also elsewhere on the board
EPD_CS: U1.P$K2 (P0.05/AIN3); also elsewhere on the board
EPD_DC: U1.P$AD10 (P0.15); also elsewhere on the board
EPD_RST: U1.P$AC11 (P0.16); also elsewhere on the board
GND: C1.2, C2.2, C3.2, C4.2, C5.2, C6.2, C7.2, C8.2, C9.2, C10.2, C11.2, C12.2, C13.2, C14.2, C15.2, C16.2, C17.1, C18.1, C19.2, C20.2, C21.2, C22.2, C23.1, C24.1, C25.2, C33.2, C37.1, C38.1, C39.2, IC1.D2 (GND), IC3.8 (GNDIO), IC3.9 (GND), IC9.B1 (VSEL), IC9.C1 (AGND), IC9.C2 (PGND_1), IC9.C3 (PGND_2), J2.3, J2.5, R3.1, R9.1, TP_GND.TP, U1.P$74 (VSS_PAD), U1.P$75 (VSS_PAD), U1.P$76 (VSS_PAD), U1.P$77 (VSS_PAD), U1.P$78 (VSS_PAD), U1.P$79 (VSS_PAD), U1.P$80 (VSS_PAD), U1.P$81 (VSS_PAD), U1.P$82 (VSS_PAD), U1.P$83 (VSS_PAD), U1.P$84 (VSS_PAD), U1.P$85 (VSS_PAD), U1.P$86 (VSS_PAD), U1.P$87 (VSS_PAD), U1.P$88 (VSS_PAD), U1.P$89 (VSS_PAD), U1.P$90 (VSS_PAD), U1.P$B7 (VSS), U1.P$F23 (VSS_PA), X1.2, X1.4; also elsewhere on the board
HAPTIC_EN: U1.P$U1 (P0.12); also elsewhere on the board
IMU_INT1: IC3.5 (INT1), U1.P$N1 (P0.08)
IMU_INT2: IC3.6 (INT2), U1.P$P2 (P1.08)
LX1: IC9.B2 (SW1_1), IC9.B3 (SW1_2), L7.1
LX2: IC9.D2 (SW2_1), IC9.D3 (SW2_2), L7.2
MOSI: U1.P$B13 (P0.03/AIN1); also elsewhere on the board
unnamed: IC1.D1 (TS/MR), R9.2
unnamed: C11.1, U1.P$D23 (DEC3)
unnamed: IC9.D1 (SCL), R4.2
unnamed: IC9.E1 (SDA), R2.2
unnamed: C18.2, U1.P$F2 (P0.01/XL2), X2.2
unnamed: C17.2, U1.P$D2 (P0.00/XL1), X2.1
unnamed: IC3.1 (SDO), R3.2
unnamed: C5.1, U1.P$C1 (DEC1)
unnamed: L2.1, U1.P$B3 (DCC)
unnamed: L2.2, L3.1
unnamed: C12.1, U1.P$A22 (VDD)
unnamed: C13.1, U1.P$A18 (DEC2)
unnamed: C2.1, U1.P$A23 (XC2), X1.3
unnamed: C1.1, U1.P$B24 (XC1), X1.1
unnamed: C3.1, L1.1, U1.P$H23 (ANT)
unnamed: ANT1.1 (FEED), C4.1, C22.1, L1.2
unnamed: C9.1, U1.P$N24 (DEC5)
unnamed: C20.1, U1.P$AC5 (DEC3V3)
P0.04: U1.P$J1 (P0.04/AIN2)
P0.09: U1.P$L24 (P0.09/NFC1)
P0.13: U1.P$AD8 (P0.13)
P0.14: U1.P$AC9 (P0.14)
P0.19: U1.P$AC15 (P0.19)
P0.20: U1.P$AD16 (P0.20)
P0.21: U1.P$AC17 (P0.21)
P0.22: U1.P$AD18 (P0.22)
P0.23: U1.P$AC19 (P0.23)
P0.24: U1.P$AD20 (P0.24)
P0.25: U1.P$AC21 (P0.25)
P0.26: U1.P$G1 (P0.26)
P0.27: U1.P$H2 (P0.27)
P0.28: U1.P$B11 (P0.28/AIN4)
P0.29: U1.P$A10 (P0.29/AIN5)
P0.30: U1.P$B9 (P0.30/AIN6)
P0.31: U1.P$A8 (P0.31/AIN7)
P1.01: U1.P$Y23 (P1.01); also elsewhere on the board
P1.02: U1.P$W24 (P1.02); also elsewhere on the board
P1.03: U1.P$V23 (P1.03)
P1.04: U1.P$U24 (P1.04)
P1.05: U1.P$T23 (P1.05)
P1.06: U1.P$R24 (P1.06)
P1.07: U1.P$P23 (P1.07)
P1.09: U1.P$R1 (P1.09)
P1.10: U1.P$A20 (P1.10)
P1.11: U1.P$B19 (P1.11)
P1.12: U1.P$B17 (P1.12)
P1.13: U1.P$A16 (P1.13)
P1.14: U1.P$B15 (P1.14)
P1.15: U1.P$A14 (P1.15)
PMIC_INT: IC1.A1 (!INT), U1.P$T2 (P0.11)
RESET: J2.6, TP_RESET.TP, U1.P$AC13 (P0.18/RESET)
SCK: U1.P$A12 (P0.02/AIN0); also elsewhere on the board
SCL: IC1.B1 (SCL), IC3.12 (SCX), R4.1, R17.2, TP_SCL.TP, U1.P$M2 (P0.07); also elsewhere on the board
SDA: IC1.C1 (SDA), IC3.2 (SDX), R2.1, R18.2, TP_SDA.TP, U1.P$L1 (P0.06); also elsewhere on the board
SWDCLK: J2.4, TP_SWDCLK.TP, U1.P$AA24 (SWDCLK)
SWDIO: J2.2, TP_SWDIO.TP, U1.P$AC24 (SWDIO)
SWO: TP_SWO.TP, U1.P$AD22 (P1.00)
VBAT: C37.2, IC1.C2 (BAT); also elsewhere on the board
VBUS: C21.1, C38.2, IC1.A2 (IN), U1.P$AD2 (VBUS); also elsewhere on the board
VREG: C23.2, C24.2, C39.1, IC1.B2 (SYS), IC9.A1 (EN), IC9.A2 (VIN_1), IC9.A3 (VIN_2), TP_VREG.TP

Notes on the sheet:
LiPo Charger
DC/DC
IMU
DEC3
DEC4_6
N.C.
SWD

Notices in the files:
parts and their libraries:
COPYRIGHT: Copyright (C) 2024 Ultra Librarian. All rights reserved.
COPYRIGHT: Copyright (C) 2025 Ultra Librarian. All rights reserved.
